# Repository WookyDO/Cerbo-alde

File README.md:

# Cerbo-alde

Steuerung einer **Alde Compact 3030 Plus** oder einer **Truma Combi mit CP Plus** über den
**Cerbo GX** (Venus OS) oder eine eigene Weboberfläche, mit dem **WomoLIN LIN-Controller**
(ESP32 + TJA1021T) als Bridge am LIN-Bus der Heizung.

```
Alde 3030 Plus ── gelber RJ12 ──┐
  (Bridge = LIN-Master)         ├─ WomoLIN LIN-Controller ── WLAN/TCP ── Cerbo GX
Truma CP Plus  ── RJ12 (TIN) ───┘    Firmware: firmware/                 Dienst: cerbo/dbus-lin-heater/
  (Bridge = iNet Box, LIN-Slave)     Weboberfläche: http://lin-bridge.local
```

Der Heizungstyp wird auf der Setup-Seite der Bridge gewählt. Der Cerbo-Dienst übernimmt ihn
automatisch.

> **Status:** Protokolle und Logik sind mit Unit-Tests geprüft. Beide Typen laufen im Testbetrieb
> auf dem Controller und dem Cerbo. Der Test an einer echten Alde und an einem echten CP Plus steht
> noch aus. Erst nur lesen (siehe [Inbetriebnahme](#inbetriebnahme)), dann steuern.

## Auf dem Cerbo

**Alde Compact 3030 Plus**

| D-Bus-Dienst | Inhalt |
|---|---|
| `com.victronenergy.switch.alde_3030` | Sollwert (Temperaturregler), Gas ein/aus, Elektro 1/2/3 kW, Warmwasser Aus/An/Boost; Statuswerte unter `/Alde/*` (Pumpe, Gasventil, 230 V, Fehler) |
| `com.victronenergy.temperature.alde_innen` | Innentemperatur |
| `com.victronenergy.temperature.alde_aussen` | Außentemperatur |

**Truma Combi mit CP Plus**

| D-Bus-Dienst | Inhalt |
|---|---|
| `com.victronenergy.switch.truma_combi` | Raumtemperatur (Temperaturregler mit an/aus), Heizstufe Aus/Eco/Boost, Warmwasser Aus/Eco/Heiß/Boost, Energie Gas/Mix/Elektro, Elektro 900/1800 W; Statuswerte unter `/Truma/*` (Betriebsstatus, Fehlercode) |
| `com.victronenergy.temperature.truma_innen` | Innentemperatur |
| `com.victronenergy.temperature.truma_wasser` | Wassertemperatur |

In der GUI v2 erscheinen die Schalter in der Schalter-Ansicht (Gruppe „Alde Heizung“ bzw.
„Truma Heizung“), die Temperaturen unter Temperatursensoren und im VRM.

## Hardware

**ESP32_LIN-Platine** (ESP32-C3-WROOM-02-N4, 2× TJA1021T/20, KiCad-Projekt in [`hardware/`](hardware), Fertigungsdaten in `hardware/fertigung`):

| | Truma (Bridge = Slave) | Alde (Bridge = Master) |
|---|---|---|
| Kanal | LIN1, Klemme J2 / RJ12 J6 | LIN2, Klemme J5 / RJ12 J7, **Jumper JP1 stecken** |
| GPIO RX / TX / SLP | 5 / 6 / 7 | 4 / 10 / 20 |

- Nur der Transceiver der gewählten Heizung wird geweckt (SLP high), der andere schläft.
- Rote LED (GPIO8, aktiv low): an = Heizung verbunden und Netz da, blinkt = Setup- oder
  Notfall-Access-Point offen, aus = keine Verbindung zur Heizung. Grün = Versorgung.
- Bordspannung über VSENSE (GPIO3, Teiler 100k/15k an VIN_F): in der Weboberfläche,
  `/api/state` (`"vin"`), per Befehl `VIN` und in `NET`. Gemessen wird hinter der
  Verpolschutz-Diode; der Wert enthält dafür pauschal 0,24 V (`VSENSE_DIODE_DROP` in `config.h`,
  gemessen bei 12 V). Nur an USB ist die Anzeige nicht aussagekräftig, weil der Strom dort über
  D3 statt über D1 kommt.
- RJ12-Buchsen in Truma-Belegung: Pin 1 = 12 V (VIN_RAW), Pin 2/5 = GND, Pin 3 = LIN.
  Der gelbe Alde-Stecker hat LIN auf Pin 4 und passt deshalb nicht direkt an J7; die Alde
  über die Klemme J5 anschließen.
- Flashen und Log über USB-C (USB-Serial/JTAG des C3, keine Treiber nötig).

**WomoLIN LIN-Controller:**

- WomoLIN LIN-Controller: ESP32 (16 MB), TJA1021T, LIN an UART1 (**RX GPIO14, TX GPIO15**),
  LEDs GPIO2 (LIN) und GPIO17 (Netz). Pinbelegung aus `inetbox2mqtt` (Profil `WOMOLIN`).
- **Alde:** Anschluss am **gelben** RJ12: **Pin 4 = LIN**, **Pin 2 = GND**. Den roten (internen) Bus
  nicht verwenden.
- **Truma:** Anschluss am RJ12 des CP Plus bzw. TIN-Bus: **Pin 3 = LIN**, **Pin 5 = GND**.
  Voraussetzungen: CP Plus mit Firmware **ab C4.00.00** (ältere nur lesen), **keine echte iNet Box**
  am Bus (war je eine angeschlossen, vorher ohne Bridge einmal neu initialisieren). Getestet ist das
  Protokoll in den Quellen mit der Combi 4.
- 12 V für den Controller aus dem Bordnetz. Die Masse muss mit der Heizung verbunden sein.

## Firmware (`firmware/`)

Benötigt [PlatformIO](https://platformio.org/).

```sh
cd firmware
pio run -e esp32_lin -t upload  # ESP32_LIN: erstes Flashen per USB
pio run -e womolin -t upload    # WomoLIN: erstes Flashen per USB
pio device monitor              # Logausgabe, 115200 Baud
```

Für OTA und den Testbetrieb gibt es zu jeder Platine die Varianten `_ota`, `_sim` und `_sim_ota`
(z.B. `esp32_lin_ota`).

WLAN, IP, Passwörter und Heizungstyp werden nicht einkompiliert, sondern auf der Setup-Seite der
Bridge eingestellt (siehe [Einrichtung](#einrichtung)). Alle weiteren Updates gehen per WLAN:

```sh
export LIN_OTA_PASSWORD='…'    # OTA-Passwort aus der Setup-Seite
pio run -e womolin_ota -t upload
```

Die Originalsoftware lässt sich jederzeit wiederherstellen, über
`bin/flash_womolin_inetbox2mqtt_*.bin.zip` aus [inetbox2mqtt](https://github.com/mc0110/inetbox2mqtt).

Eine Firmware für beide Heizungen: Flash 885 KB von 6,4 MB je App-Partition (13,5 %),
RAM 50 KB von 320 KB (15 %).

### Ablauf auf dem Bus: Alde (Bridge = LIN-Master, 19200 Baud)

- Vor dem ersten Senden hört die Bridge 1,5 s auf den Bus. Die Alde-Bedienteile senden nie von
  sich aus; kommen trotzdem Daten, hängt ein anderer Master am Bus (z.B. ein Truma CP Plus). Dann
  sendet die Bridge nichts, meldet `ERR Fremder LIN-Master am Bus` und prüft alle 10 s erneut.
- Beim Start und nach Verbindungsverlust (alle 5 s) wird der Anmelde-Frame `0x3C` gesendet:
  `10 06 B2 00 DE 41 03 00`.
- Alle 500 ms wird der Info-Frame `0x1B` (PID `0x5B`) abgefragt. Das eigene Echo wird verworfen,
  die Antwort wird anhand der Checksumme erkannt.
- Ein Steuer-Frame `0x1A` geht **nur bei einem Befehl** raus, als **Read-Modify-Write** auf Basis des
  zuletzt gelesenen Zustands. Statusbits und Zone 2 bleiben unverändert. Danach wird bis zu
  5-mal abgefragt, ob das Panel den Befehl übernommen hat. Es gibt maximal 3 Sendeversuche.
- Break: `0x00` bei 9600 Baud, das sind etwa 0,94 ms bzw. 18 Bitzeiten bei 19200 Baud.

### Ablauf auf dem Bus: Truma (Bridge = iNet Box, LIN-Slave, 9600 Baud)

- Das CP Plus ist Master. Die Bridge antwortet in einer eigenen FreeRTOS-Task, damit Webserver und
  WLAN die Antwortzeit nicht verzögern.
- Anmeldung (nach „PR SET“ am CP Plus): Lesen der Kennung `0xB2` (Supplier `0x4617`, Function
  `0x1F00`), Zuweisen der Knotenadresse `0xB0` (NAD `0x03`), danach regelmäßig `0xB9`.
- Das CP Plus schickt seinen Status als Puffer `0x14/0x33` über den Transport-Layer (`0x3C`,
  Dienst `0xBB`, 7 Frames). Temperaturen sind Kelvin × 10.
- Auf PID `0x18` meldet die Bridge `FF`, wenn ein Befehl bereitliegt, sonst `FE`. Das CP Plus holt
  ihn dann mit `0xBA` ab (Puffer `0x0C/0x32` auf `0x3D`). Unveränderte Felder werden aus dem
  letzten Status übernommen.
- Das CP Plus fragt nicht ständig; Pausen von 15–25 s sind normal. Bis ein Befehl im Status
  bestätigt ist, können ~30 s vergehen. Ohne Bestätigung nach 60 s wird er erneut eingereiht,
  insgesamt 3 Versuche.
- Regeln des CP Plus, die die Bridge selbst ergänzt: Raumtemperatur und Heizstufe gehören
  zusammen (Sollwert ab 5 °C schaltet Eco ein, Heizstufe „aus“ setzt den Sollwert auf 0), ebenso
  Energie und Leistung (Gas = 0 W, Mix/Elektro = 900 oder 1800 W).

### Zeilenprotokoll (TCP-Port 7020 und USB-Seriell)

Beim Verbinden meldet die Bridge `HELLO lin-bridge 1.1 heater=alde` bzw. `heater=truma`.
Zeilen mit `#` sind Logausgaben.

| Richtung | Zeile | Bedeutung |
|---|---|---|
| → | `GET` / `PING` | Zustand senden / `PONG` |
| → | `SET …` | siehe unten, beliebige Teilmenge |
| ← | `STATE link=1 …` | bei Änderung, sonst alle 5 s |
| ← | `STATE link=0` | Heizung antwortet nicht |
| ← | `OK` / `ERR <Text>` | Befehl angenommen / abgelehnt oder nicht übernommen |

| Heizung | `SET` | `STATE` |
|---|---|---|
| Alde | `sp` 5–30 °C (0,5er Schritte), `gas` 0/1, `el` 0–3 kW, `ww` 0=aus 1=an 2=Boost | `STATE link=1 z1=21.0 z2=- out=8.0 sp=20.0 gas=1 valve=1 el=2 ww=1 on=1 busy=0 err=0 ac=1 pump=1 raw=DE9E29` |
| Truma | `sp` 0 oder 5–30 °C, `mode` off/eco/boost, `ww` 0/40/60/200 (aus/Eco/heiß/Boost), `mix` gas/mix/el, `el` 0/900/1800 W | `STATE link=1 room=19.5 sp=21.0 mode=eco water=48.0 ww=60 mix=gas el=0 status=5 err=0` |

Typspezifische Befehle: `DIAG` (Alde: Anmelde-Frame erneut senden), `LINLOG 1`/`LINLOG 0`
(Truma: alle Frames am Bus als Logzeilen ausgeben).

Zum Testen: `nc <ip> 7020` oder den seriellen Monitor verwenden. Die Bridge hält nur eine
TCP-Verbindung; eine neue verdrängt die bestehende (z.B. die des Cerbo).

### Weboberfläche (Betrieb ohne Cerbo)

Unter `http://lin-bridge.local` (oder der IP der Bridge) gibt es eine Seite mit dem gleichen
Umfang wie auf dem Cerbo, passend zum Heizungstyp. Dazu kommen die WLAN-Signalstärke und ein Link
zu den Einstellungen. Befehle laufen über denselben Weg wie die vom Cerbo; beide lassen sich
gleichzeitig verwenden.

| Pfad | Methode | Inhalt |
|---|---|---|
| `/` | GET | Weboberfläche |
| `/api/state` | GET | `{"type":"alde"\|"truma","state":{…}\|null,"pending":bool,"error":"…","rssi":-67,"ap":bool}` |
| `/api/set` | POST | Formularfelder wie bei `SET`; Antwort `{"ok":true}` oder `{"ok":false,"error":"…"}` |
| `/setup` | GET | Einstellungen |
| `/api/config` | GET / POST | Einstellungen lesen (ohne Passwörter) / speichern |
| `/api/scan` | GET | WLAN-Suche, so lange abfragen bis `"scanning":false` |

Mit einem Web-Passwort (Setup-Seite) sind alle Seiten geschützt, Benutzer `admin`. Ohne ist die
Bridge für jeden im selben WLAN bedienbar, auch die Einstellungen.

### Einrichtung

Die Einstellungen liegen im Flash der Bridge (NVS) und überstehen Firmware-Updates.

| Einstellung | Bedeutung |
|---|---|
| Heizung | Alde Compact 3030 Plus oder Truma Combi mit CP Plus. Ein Wechsel startet die Bridge neu. |
| Betriebsart | **WLAN-Client**: Die Bridge verbindet sich mit dem Router. **Eigener Access Point**: Die Bridge öffnet dauerhaft ein eigenes WLAN, IP `192.168.4.1`. Der Cerbo verbindet sich dann mit diesem WLAN und bekommt `host = 192.168.4.1` in `config.ini`. |
| WLAN | Netzwerk (mit Suche) und Passwort |
| IP-Adresse | DHCP oder fest (IP, Gateway, Subnetzmaske, DNS). Eine feste Adresse muss außerhalb des DHCP-Bereichs liegen, bei der Fritzbox standardmäßig `.20`–`.200`. |
| Access Point | Name (Standard `LIN-Bridge`) und Passwort (Standard `lin-setup`, solange kein eigenes gesetzt ist) |
| OTA-Passwort | Pflicht. Updates per WLAN sind erst nach der Einrichtung möglich, nie ohne Passwort. |
| Web-Passwort | optional, Benutzer `admin` |

Speichern ohne Änderung tut nichts. Neue OTA- oder Web-Passwörter gelten sofort. Bei allem anderen
startet die Bridge neu; die Seite wartet, bis sie wieder antwortet.

**Erster Start:** Ohne gespeicherte Einstellungen öffnet die Bridge den Access Point `LIN-Bridge`
(Passwort `lin-setup`). Nach dem Verbinden öffnen die meisten Handys die Setup-Seite von selbst,
sonst `http://192.168.4.1` aufrufen.

**Notfall-Zugang:** Ist das eingestellte WLAN 60 s nicht erreichbar (falsches Passwort, Router aus),
öffnet die Bridge zusätzlich ihren Access Point und versucht alle 30 s erneut, ins WLAN zu kommen.
Sobald das klappt und niemand mehr am Access Point hängt, schließt sie ihn wieder. Die Netz-LED
blinkt, solange der Access Point offen ist.

**Rettung über USB:** Ist die Bridge nicht mehr erreichbar, nimmt sie über die USB-Schnittstelle
(115200 Baud) diese Befehle an. Über TCP sind sie gesperrt.

| Befehl | Wirkung |
|---|---|
| `NET` | Betriebsart, WLAN, IP-Adressen und Heizungstyp anzeigen |
| `NET STA` | zurück auf WLAN-Client (gespeichertes WLAN), Neustart |
| `NET AP` | auf dauerhaften Access Point (braucht ein gespeichertes AP-Passwort), Neustart |

Nach einer Änderung der Adresse `host` in `config.ini` auf dem Cerbo anpassen.

## Cerbo-Dienst (`cerbo/dbus-lin-heater/`)

Voraussetzung ist SSH-Zugang als root: Einstellungen → Allgemein → Zugriffsebene „Superuser“,
Root-Passwort setzen, SSH im LAN aktivieren.

```sh
scp -r cerbo/dbus-lin-heater root@<cerbo-ip>:/data/
ssh root@<cerbo-ip> /data/dbus-lin-heater/install.sh
ssh root@<cerbo-ip> vi /data/dbus-lin-heater/config.ini   # host = IP der Bridge
ssh root@<cerbo-ip> svc -t /service/dbus-lin-heater       # neu starten
```

- Heizungstyp: Mit `heater = auto` (Standard) übernimmt der Dienst den Typ aus dem `HELLO` der
  Bridge. Meldet sie einen anderen als den laufenden, merkt er ihn sich und startet mit den
  passenden D-Bus-Diensten neu. Mit `heater = alde` oder `truma` bleibt er fest; ein abweichender
  Typ wird dann nur gemeldet und nicht ausgewertet.
- Truma: Nach einer Eingabe in der GUI hält der Dienst den neuen Wert 40 s, bis das CP Plus ihn
  bestätigt hat (Alde: 3 s).
- Logs: `tail -F /var/log/dbus-lin-heater/current | tai64nlocal`
- Deinstallieren: `/data/dbus-lin-heater/uninstall.sh`
- Der Dienst übersteht Firmware-Updates, weil er unter `/data` liegt und über `/data/rc.local` gestartet wird.

## Inbetriebnahme

**Alde**

1. Controller flashen, über den Access Point `LIN-Bridge` einrichten, Heizung „Alde“ wählen.
2. Mit der Alde verbinden. Nach `Panel antwortet` sollten `STATE link=1 …`-Zeilen erscheinen.
   Die Werte mit dem Display der Alde vergleichen.
3. Einen einzelnen Befehl testen, z.B. über die Weboberfläche den Sollwert ändern, und am Panel prüfen.
4. Danach den Cerbo-Dienst installieren.

Erscheint dauerhaft `STATE link=0`, prüfe Verdrahtung, Masse und 12 V. Hilft das nicht, mit
einem Logikanalysator am LIN-Pin Break und Antwort prüfen.

**Truma**

1. Controller flashen, einrichten, Heizung „Truma“ wählen.
2. An das CP Plus anschließen und mit `LINLOG 1` (USB oder `nc <ip> 7020`) mithören. Es sollten
   Header `18`, `3C` und `3D` erscheinen. Kommt nach 60 s nichts, meldet die Weboberfläche
   „Kein CP Plus gefunden“.
3. Am CP Plus im Einstellungsmenü **„PR SET“** ausführen. Das Display zeigt „INIT…“, danach steht im
   Menü ein dritter Eintrag `inetbox`. Die Bridge meldet `CP Plus verbunden`.
4. Werte mit dem CP Plus vergleichen, dann einzelne Befehle testen. Bis zur Bestätigung können
   ~30 s vergehen.
5. Danach den Cerbo-Dienst installieren.

### Testbetrieb ohne Heizung

```sh
cd firmware
pio run -e womolin_sim -t upload        # per USB
pio run -e womolin_sim_ota -t upload    # per WLAN
```

- **Alde:** Der Controller beantwortet seine LIN-Abfragen selbst wie ein Alde-Panel. Die Antworten
  laufen über den echten Transceiver und kommen als Echo zurück; Steuer-Frames liest das simulierte
  Panel ebenfalls aus dem Echo. Damit lassen sich LIN-Hardware, WLAN/TCP und der Cerbo-Dienst
  testen. Der Controller braucht dafür 12 V, sonst bleibt es bei `link=0`. Das Panel startet mit
  18 °C innen, 8 °C außen und Sollwert 20 °C und heizt bei Gas oder Elektro mit 0,05 °C/s.
- **Truma:** Ein simuliertes CP Plus spielt den kompletten Transport-Layer in Software gegen die
  iNet Box durch, ohne Bus. Damit lassen sich Weboberfläche, TCP und Cerbo-Dienst testen, nicht aber
  der LIN-Slave-Treiber. Start: 15 °C innen, Wasser 20 °C, Heizung aus.

Die Testvariante **nicht an der echten Heizung** verwenden. Vor dem Anschluss wieder
`pio run -e womolin -t upload` (oder per WLAN `womolin_ota`) aufspielen.

## Tests

```sh
cd cerbo/dbus-lin-heater && python3 -m unittest discover -s tests   # Cerbo-Dienst
cd firmware && pio test -e native                                    # Protokolle (C++)
```

## Quellen

- [daviddootson/alde_3030_plus](https://github.com/daviddootson/alde_3030_plus): Protokoll des
  CI-Busses der 3030 Plus (Mitschnitte, Anmelde-Frame, Bitbelegung)
- [danielfett/inetbox.py](https://github.com/danielfett/inetbox.py): Protokoll der Truma iNet Box
  (Transport-Layer, Puffer, Prüfsumme, Referenzwerte für die Tests). Der Code hier ist eine eigene
  Umsetzung nach dieser Beschreibung; inetbox.py steht unter GPL-3.0.
- [mc0110/inetbox2mqtt](https://github.com/mc0110/inetbox2mqtt): Pinbelegung des WomoLIN-Controllers,
  Voraussetzungen und Einrichtung am CP Plus
- [WomoLIN](https://github.com/muccc/WomoLIN): Grundlagen zum LIN-Bus im Wohnmobil
- [victronenergy/gui-v2](https://github.com/victronenergy/gui-v2): Schnittstelle `SwitchableOutput`

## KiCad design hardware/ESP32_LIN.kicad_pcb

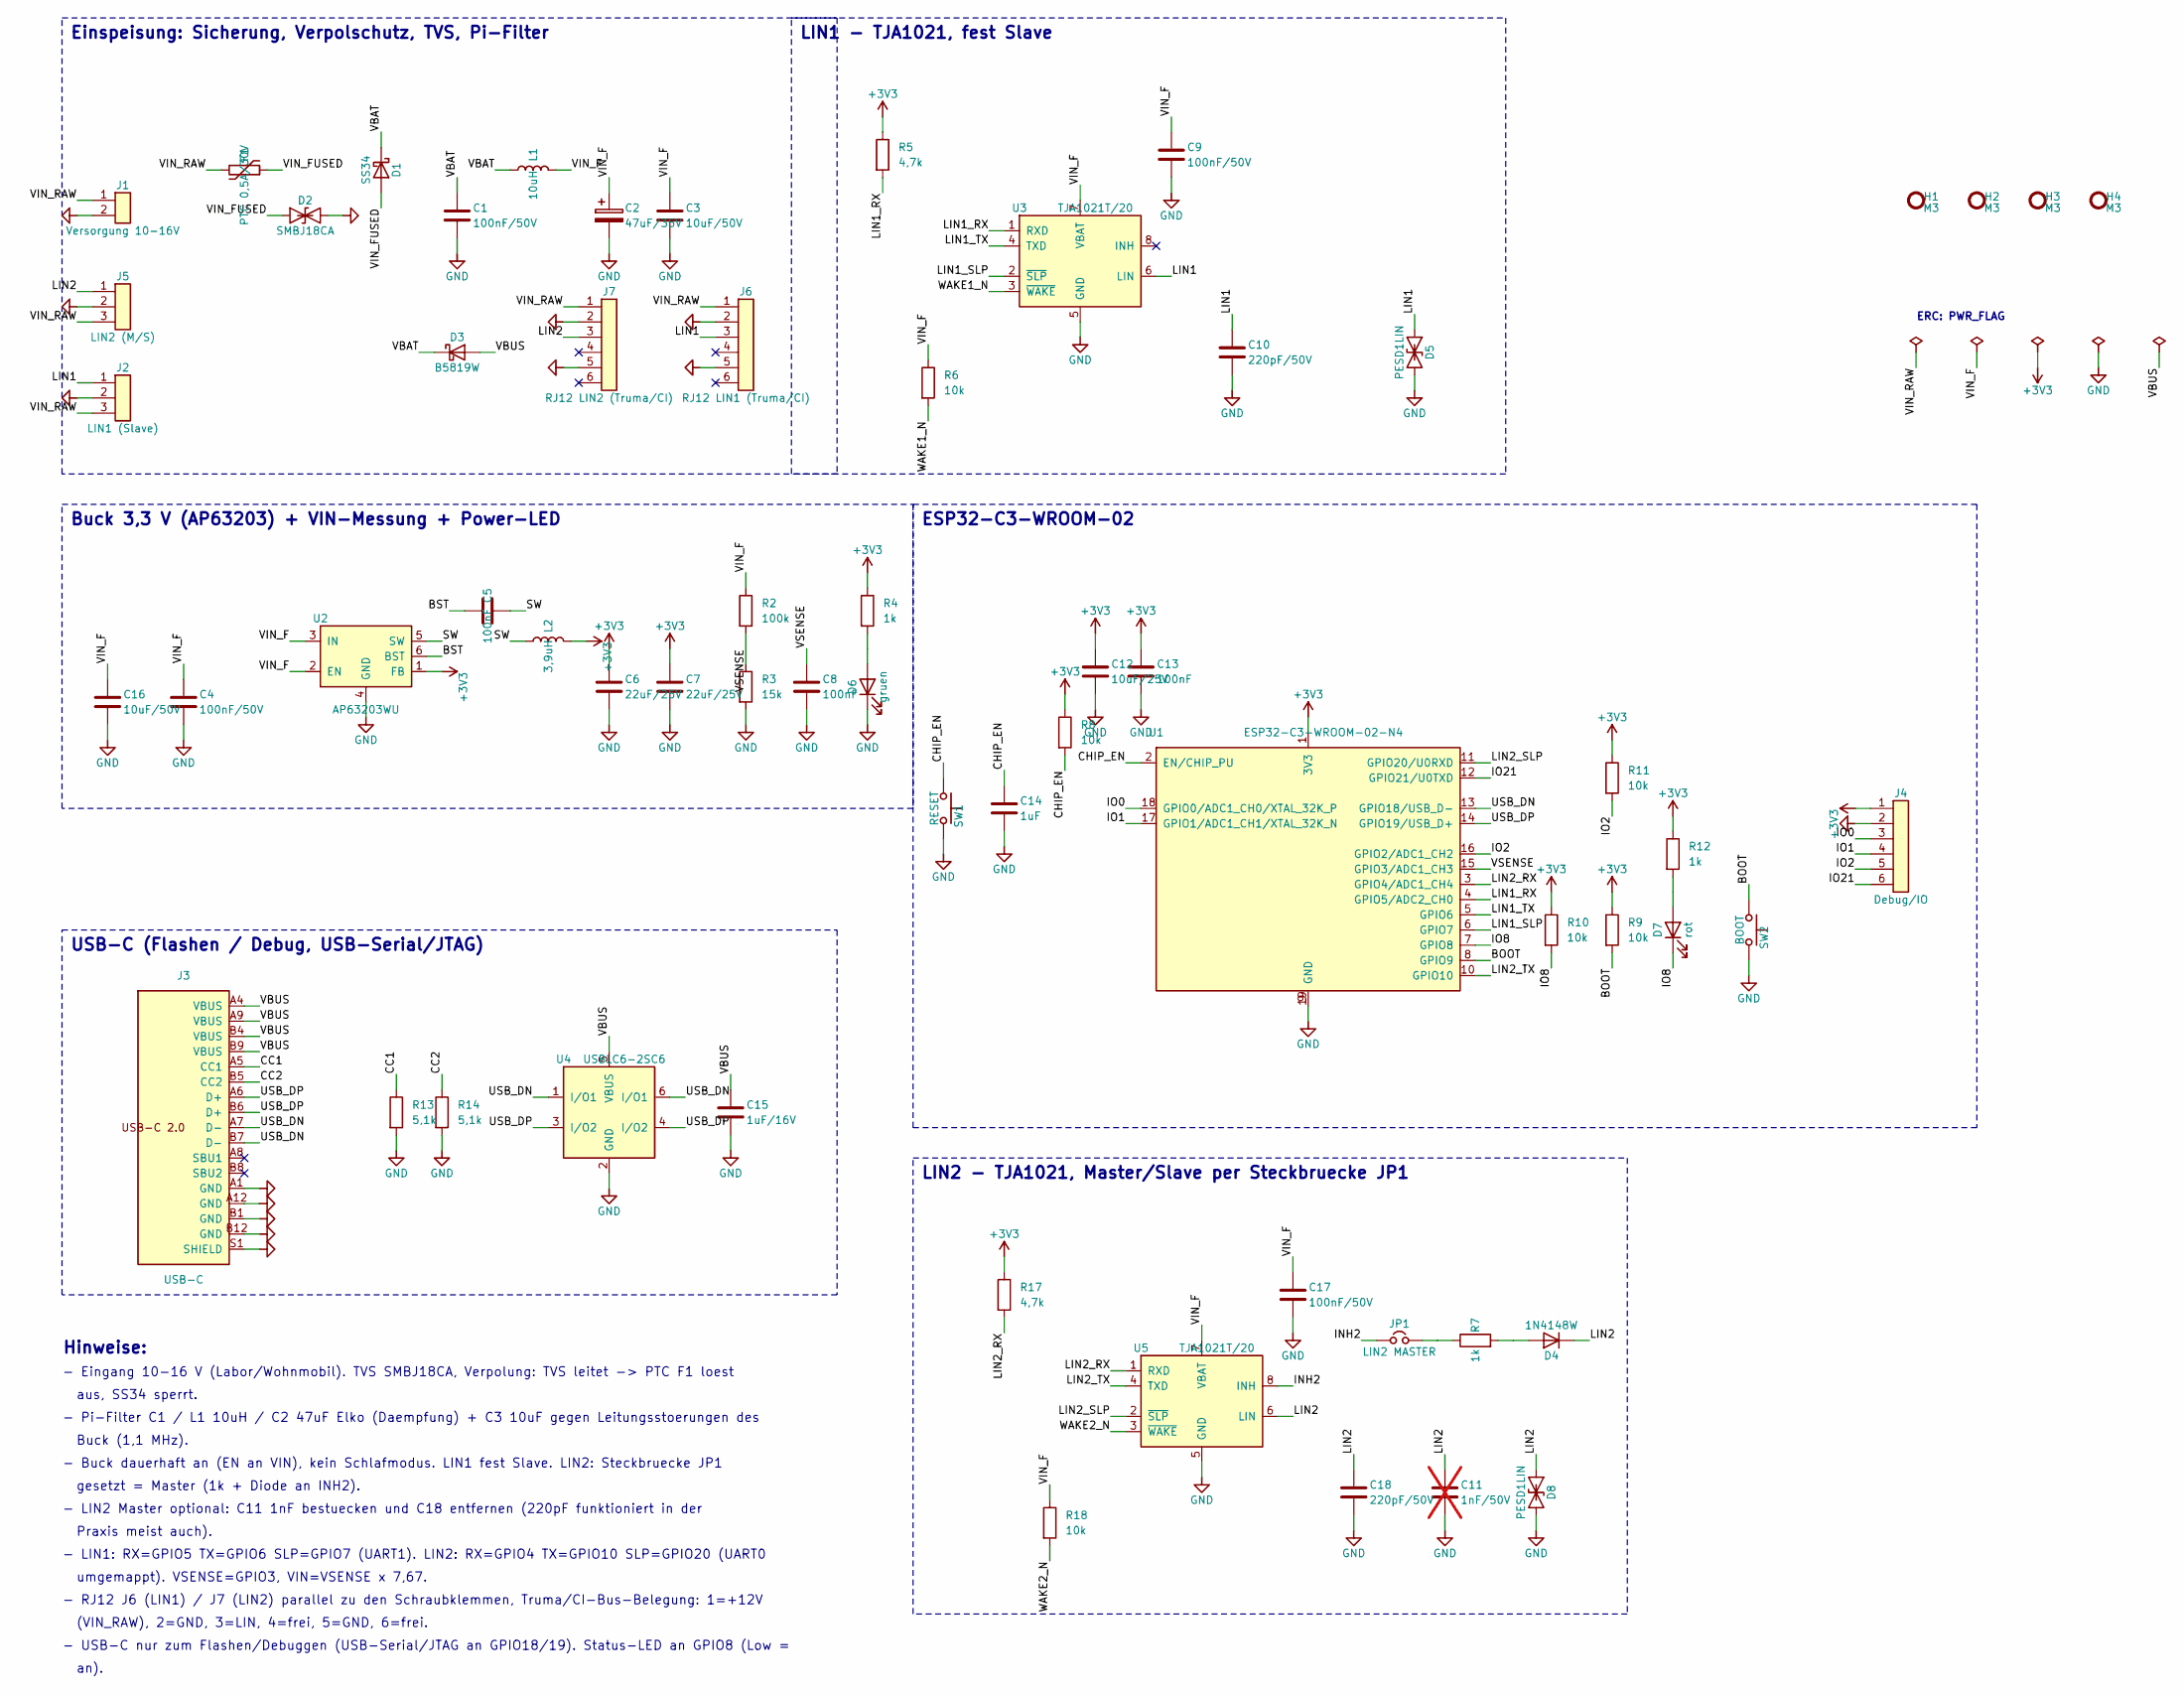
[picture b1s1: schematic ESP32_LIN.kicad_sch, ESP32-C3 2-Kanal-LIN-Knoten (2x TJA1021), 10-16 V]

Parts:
C1, C4, C9, C17: 100nF/50V; C_0603_1608Metric; MPN CC0603KRX7R9BB104; LCSC C14663
C2: 47uF/35V; CP_Elec_6.3x7.7; MPN VEJ470M1VTR-0607; LCSC C122665
C3, C16: 10uF/50V; C_1210_3225Metric; MPN CL32B106KBJNNNE; LCSC C138687
C5, C8, C13: 100nF; C_0603_1608Metric; MPN CC0603KRX7R9BB104; LCSC C14663
C6, C7: 22uF/25V; C_1206_3216Metric; MPN CL31A226KAHNNNE; LCSC C12891
C10, C18: 220pF/50V; C_0603_1608Metric; MPN CL10B221KB8NNNC; LCSC C1603
C11: 1nF/50V; C_0603_1608Metric; MPN CL10B102KB8NNNC; LCSC C1588; not fitted
C12: 10uF/25V; C_0805_2012Metric; MPN CL21A106KAYNNNE; LCSC C15850
C14: 1uF; C_0603_1608Metric; MPN CL10A105KB8NNNC; LCSC C15849
C15: 1uF/16V; C_0603_1608Metric; MPN CL10A105KB8NNNC; LCSC C15849
D1: SS34; D_SMA; MPN SS34; LCSC C115205
D2: SMBJ18CA; D_SMB; MPN SMBJ18CA; LCSC C113991
D3: B5819W; D_SOD-123; MPN B5819W; LCSC C109213
D4: 1N4148W; D_SOD-123; MPN 1N4148W; LCSC C109203
D5, D8: PESD1LIN; D_SOD-323; MPN PESD1LIN; LCSC C393615
D6: gruen; LED_0603_1608Metric; MPN LTST-C190KGKT; LCSC C125094
D7: rot; LED_0603_1608Metric; MPN KT-0603R; LCSC C2286
F1: PTC 0,5A/30V; Fuse_1812_4532Metric; MPN 1812L050/60GR; LCSC C19078719
H1, H2, H3, H4: M3; MountingHole_3.2mm_M3
J1: Versorgung 10-16V; TerminalBlock_Phoenix_MKDS-1,5-2-5.08_1x02_P5.08mm_Horizont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; MPN KF128-5.08-2P-AA; LCSC C474952
J2: LIN1 (Slave); TerminalBlock_Phoenix_MKDS-1,5-3-5.08_1x03_P5.08mm_Horizont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; MPN KF128-5.08-3P-AA; LCSC C474953
J3: USB-C; USB_C_Receptacle_HRO_TYPE-C-31-M-12; MPN TYPE-C-31-M-12; LCSC C165948
J4: Debug/IO; PinHeader_1x06_P2.54mm_Vertical; MPN B-2100S06P-A110; LCSC C124380
J5: LIN2 (M/S); TerminalBlock_Phoenix_MKDS-1,5-3-5.08_1x03_P5.08mm_Horizont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; MPN KF128-5.08-3P-AA; LCSC C474953
J6: RJ12 LIN1 (Truma/CI); TYCO_5555165-1; MPN 5555165-1; LCSC C305981
J7: RJ12 LIN2 (Truma/CI); TYCO_5555165-1; MPN 5555165-1; LCSC C305981
JP1: LIN2 MASTER; PinHeader_1x02_P2.54mm_Vertical; MPN B-2100S02P-A110; LCSC C124375
L1: 10uH; L_Bourns_SRN6045TA; MPN SMNR6045-100MT; LCSC C135304
L2: 3,9uH; L_Bourns-SRN4018; MPN SWPA4030S3R9MT; LCSC C96899
R2: 100k; R_0603_1608Metric; MPN 0603WAF1003T5E; LCSC C25803
R3: 15k; R_0603_1608Metric; MPN 0603WAF1502T5E; LCSC C22809
R4, R12: 1k; R_0603_1608Metric; MPN 0603WAF1001T5E; LCSC C21190
R5, R17: 4,7k; R_0603_1608Metric; MPN 0603WAF4701T5E; LCSC C23162
R6, R8, R9, R10, R11, R18: 10k; R_0603_1608Metric; MPN 0603WAF1002T5E; LCSC C25804
R7: 1k; R_1206_3216Metric; MPN 1206W4F1001T5E; LCSC C4410
R13, R14: 5,1k; R_0603_1608Metric; MPN 0603WAF5101T5E; LCSC C23186
SW1: RESET; SW_SPST_B3U-1000P; MPN B3U-1000P; LCSC C231329
SW2: BOOT; SW_SPST_B3U-1000P; MPN B3U-1000P; LCSC C231329
U1: ESP32-C3-WROOM-02-N4; ESP32-C3-WROOM-02; MPN ESP32-C3-WROOM-02-N4
U2: AP63203WU; TSOT-23-6; MPN AP63203WU-7; LCSC C780769
U3, U5: TJA1021T/20; SOIC-8_3.9x4.9mm_P1.27mm; MPN TJA1021T/20/CM,118; LCSC C128810
U4: USBLC6-2SC6; SOT-23-6; MPN USBLC6-2SC6; LCSC C21713975

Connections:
+3V3: C6.1, C7.1, C12.1, C13.1, J4.1, L2.2, R4.1, R5.1, R8.1, R9.1, R10.1, R11.1, R12.1, R17.1, U1.1 (3V3), U2.1 (FB)
BOOT: R9.2, SW2.1, U1.8 (GPIO9)
BST: C5.1, U2.6 (BST)
CC1: J3.A5 (CC1), R13.1
CC2: J3.B5 (CC2), R14.1
CHIP_EN: C14.1, R8.2, SW1.1, U1.2 (EN/CHIP_PU)
GND: C1.2, C2.2, C3.2, C4.2, C6.2, C7.2, C8.2, C9.2, C10.2, C11.2, C12.2, C13.2, C14.2, C15.2, C16.2, C17.2, C18.2, D2.2 (A2), D5.2 (A2), D6.1 (K), D8.2 (A2), J1.2, J2.2, J3.A1 (GND), J3.A12 (GND), J3.B1 (GND), J3.B12 (GND), J3.S1 (SHIELD), J4.2, J5.2, J6.2, J6.5, J7.2, J7.5, R3.2, R13.2, R14.2, SW1.2, SW2.2, U1.9 (GND), U1.19 (GND), U2.4 (GND), U3.5 (GND), U4.2 (GND), U5.5 (GND)
INH2: JP1.1 (A), U5.8 (INH)
IO0: J4.3, U1.18 (GPIO0/ADC1_CH0/XTAL_32K_P)
IO1: J4.4, U1.17 (GPIO1/ADC1_CH1/XTAL_32K_N)
IO2: J4.5, R11.2, U1.16 (GPIO2/ADC1_CH2)
IO8: D7.1 (K), R10.2, U1.7 (GPIO8)
IO21: J4.6, U1.12 (GPIO21/U0TXD)
LIN1: C10.1, D5.1 (A1), J2.1, J6.3, U3.6 (LIN)
LIN1_RX: R5.2, U1.4 (GPIO5/ADC2_CH0), U3.1 (RXD)
LIN1_SLP: U1.6 (GPIO7), U3.2 (~SLP)
LIN1_TX: U1.5 (GPIO6), U3.4 (TXD)
LIN2: C11.1, C18.1, D4.1 (K), D8.1 (A1), J5.1, J7.3, U5.6 (LIN)
LIN2_PU: JP1.2 (B), R7.1
LIN2_PU2: D4.2 (A), R7.2
LIN2_RX: R17.2, U1.3 (GPIO4/ADC1_CH4), U5.1 (RXD)
LIN2_SLP: U1.11 (GPIO20/U0RXD), U5.2 (~SLP)
LIN2_TX: U1.10 (GPIO10), U5.4 (TXD)
PWR_LED: D6.2 (A), R4.2
STAT_LED: D7.2 (A), R12.2
SW: C5.2, L2.1, U2.5 (SW)
USB_DN: J3.A7 (D-), J3.B7 (D-), U1.13 (GPIO18/USB_D-), U4.1 (I/O1), U4.6 (I/O1)
USB_DP: J3.A6 (D+), J3.B6 (D+), U1.14 (GPIO19/USB_D+), U4.3 (I/O2), U4.4 (I/O2)
VBAT: C1.1, D1.1 (K), D3.1 (K), L1.1
VBUS: C15.1, D3.2 (A), J3.A4 (VBUS), J3.A9 (VBUS), J3.B4 (VBUS), J3.B9 (VBUS), U4.5 (VBUS)
VIN_F: C2.1, C3.1, C4.1, C9.1, C16.1, C17.1, L1.2, R2.1, R6.1, R18.1, U2.2 (EN), U2.3 (IN), U3.7 (VBAT), U5.7 (VBAT)
VIN_FUSED: D1.2 (A), D2.1 (A1), F1.2
VIN_RAW: F1.1, J1.1, J2.3, J5.3, J6.1, J7.1
VSENSE: C8.1, R2.2, R3.1, U1.15 (GPIO3/ADC1_CH3)
WAKE1_N: R6.2, U3.3 (~WAKE)
WAKE2_N: R18.2, U5.3 (~WAKE)

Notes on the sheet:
ERC: PWR_FLAG
Einspeisung: Sicherung, Verpolschutz, TVS, Pi-Filter
Buck 3,3 V (AP63203) + VIN-Messung + Power-LED
LIN1 - TJA1021, fest Slave
LIN2 - TJA1021, Master/Slave per Steckbruecke JP1
ESP32-C3-WROOM-02
USB-C (Flashen / Debug, USB-Serial/JTAG)
Hinweise:
- Eingang 10-16 V (Labor/Wohnmobil). TVS SMBJ18CA, Verpolung: TVS leitet -> PTC F1 loest
aus, SS34 sperrt.
- Pi-Filter C1 / L1 10uH / C2 47uF Elko (Daempfung) + C3 10uF gegen Leitungsstoerungen des
Buck (1,1 MHz).
- Buck dauerhaft an (EN an VIN), kein Schlafmodus. LIN1 fest Slave. LIN2: Steckbruecke JP1
gesetzt = Master (1k + Diode an INH2).
- LIN2 Master optional: C11 1nF bestuecken und C18 entfernen (220pF funktioniert in der
Praxis meist auch).
- LIN1: RX=GPIO5 TX=GPIO6 SLP=GPIO7 (UART1). LIN2: RX=GPIO4 TX=GPIO10 SLP=GPIO20 (UART0
umgemappt). VSENSE=GPIO3, VIN=VSENSE x 7,67.
- RJ12 J6 (LIN1) / J7 (LIN2) parallel zu den Schraubklemmen, Truma/CI-Bus-Belegung: 1=+12V
(VIN_RAW), 2=GND, 3=LIN, 4=frei, 5=GND, 6=frei.
- USB-C nur zum Flashen/Debuggen (USB-Serial/JTAG an GPIO18/19). Status-LED an GPIO8 (Low =
an).

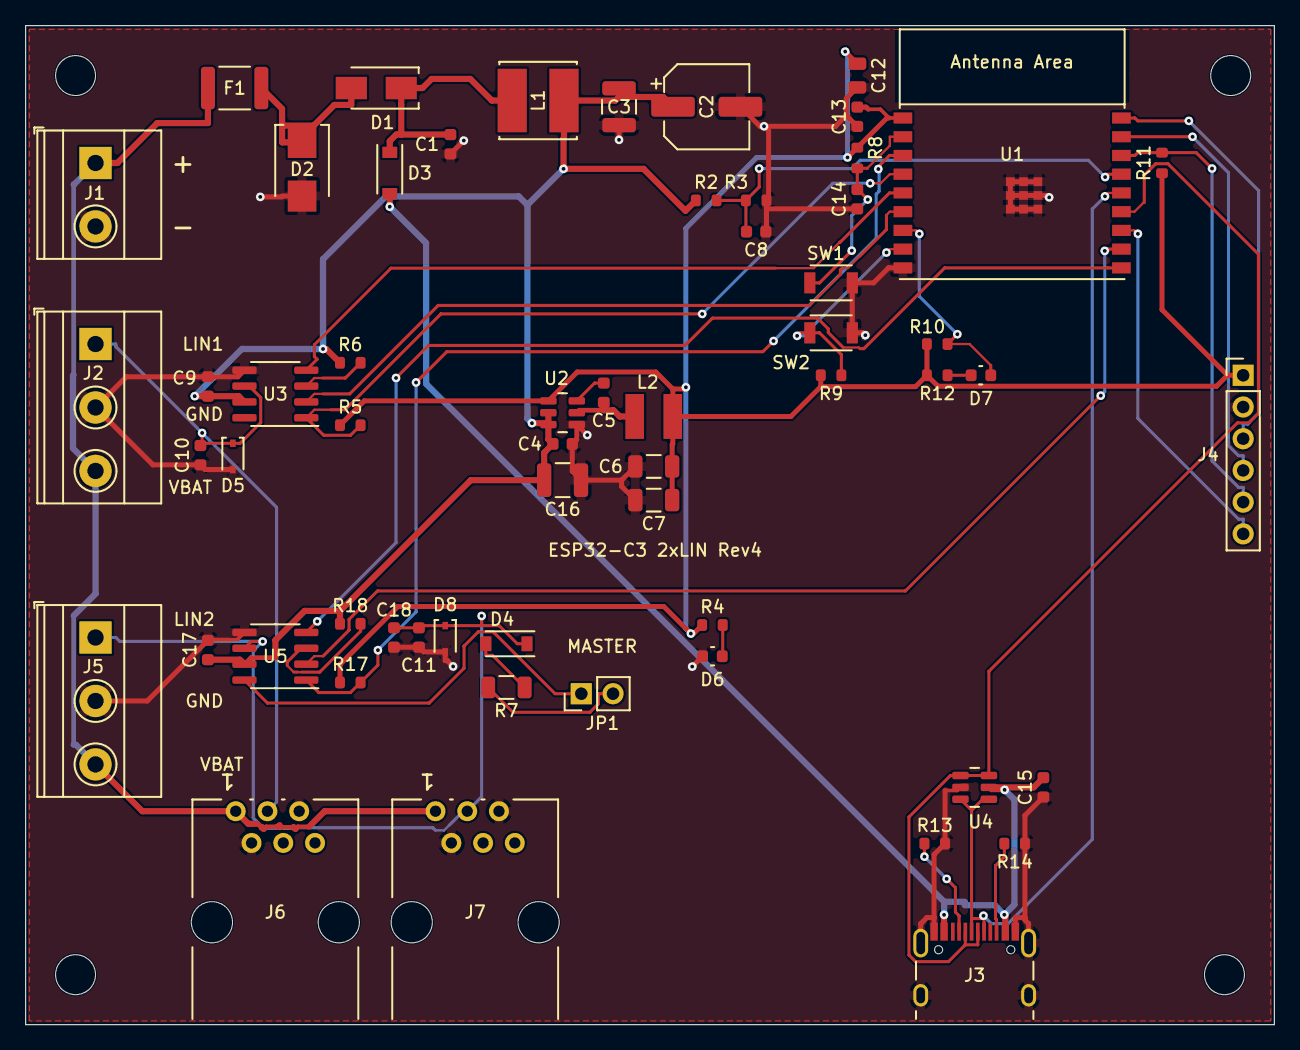
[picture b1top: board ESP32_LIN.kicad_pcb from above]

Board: 2 copper layers, 100.0 x 80.0 mm, 63 parts (0 on the bottom side), 36 nets.

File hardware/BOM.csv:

Referenzen;Anzahl;Wert;Footprint;LCSC;Hersteller-Teil;Hersteller;Bestueckung
SW1, SW2;2;B3U-1000P;SW_SPST_B3U-1000P;C231329;B3U-1000P;Omron;JLCPCB
D3;1;B5819W;D_SOD-123;C109213;B5819W;MDD;JLCPCB
R5, R17;2;4.7kΩ;R_0603_1608Metric;C23162;0603WAF4701T5E;UNI-ROYAL;JLCPCB
C6, C7;2;22uF 25V X5R;C_1206_3216Metric;C12891;CL31A226KAHNNNE;Samsung;JLCPCB
U1;1;ESP32-C3 Modul;ESP32-C3-WROOM-02;;ESP32-C3-WROOM-02-N4;Espressif;selbst beschaffen/loeten
C1, C4, C5, C8, C9, C13, C17;7;100nF 50V X7R;C_0603_1608Metric;C14663;CC0603KRX7R9BB104;YAGEO;JLCPCB
R6, R8, R9, R10, R11, R18;6;10kΩ;R_0603_1608Metric;C25804;0603WAF1002T5E;UNI-ROYAL;JLCPCB
J4;1;Stiftleiste 1x6 2,54 mm;PinHeader_1x06_P2.54mm_Vertical;;PREC006SAAN-RC;Sullins;selbst beschaffen/loeten
JP1;1;Stiftleiste 1x2 2,54 mm;PinHeader_1x02_P2.54mm_Vertical;;PREC002SAAN-RC;Sullins;selbst beschaffen/loeten
C3, C16;2;10uF 50V X7R;C_1210_3225Metric;C138687;CL32B106KBJNNNE;Samsung;JLCPCB
R13, R14;2;5.1kΩ;R_0603_1608Metric;C23186;0603WAF5101T5E;UNI-ROYAL;JLCPCB
J2, J5;2;Schraubklemme 3-pol. 5,08 mm;TerminalBlock_Phoenix_MKDS-1,5-3-5.08_1x03_P5.08mm_Horizontal;;1715734;Phoenix Contact;selbst beschaffen/loeten
J6, J7;2;RJ12 6P6C liegend;TYCO_5555165-1;;5555165-1;TE Connectivity;selbst beschaffen/loeten
D5, D8;2;PESD1LIN;D_SOD-323;C393615;PESD1LIN;DOWO;JLCPCB
F1;1;PTC 0.5A 60V;Fuse_1812_4532Metric;C19078719;1812L050/60GR;Littelfuse;JLCPCB
L2;1;3.9uH;L_Bourns-SRN4018;C96899;SWPA4030S3R9MT;Sunlord;JLCPCB
J3;1;TYPE-C-31-M-12;USB_C_Receptacle_HRO_TYPE-C-31-M-12;C165948;TYPE-C-31-M-12;Korean Hroparts;JLCPCB
C2;1;47uF 35V;CP_Elec_6.3x7.7;C122665;VEJ470M1VTR-0607;Lelon;JLCPCB
U4;1;USBLC6-2SC6;SOT-23-6;C21713975;USBLC6-2SC6;ST;JLCPCB
D4;1;1N4148W;D_SOD-123;C109203;1N4148W;MDD;JLCPCB
R3;1;15kΩ;R_0603_1608Metric;C22809;0603WAF1502T5E;UNI-ROYAL;JLCPCB
U3, U5;2;TJA1021T/20;SOIC-8_3.9x4.9mm_P1.27mm;C128810;TJA1021T/20/CM,118;NXP;JLCPCB
D6;1;LED green;LED_0603_1608Metric;C125094;LTST-C190KGKT;Lite-On;JLCPCB
D1;1;SS34;D_SMA;C115205;SS34;MDD;JLCPCB
C11;1;1nF/50V;C_0603_1608Metric;C1588;CL10B102KB8NNNC;Samsung;NICHT bestuecken
R7;1;1kΩ 0.25W;R_1206_3216Metric;C4410;1206W4F1001T5E;UNI-ROYAL;JLCPCB
L1;1;10uH;L_Bourns_SRN6045TA;C135304;SMNR6045-100MT;Sunlord;JLCPCB
U2;1;AP63203WU-7;TSOT-23-6;C780769;AP63203WU-7;Diodes;JLCPCB
C10, C18;2;220pF 50V X7R;C_0603_1608Metric;C1603;CL10B221KB8NNNC;Samsung;JLCPCB
D2;1;SMBJ18CA;D_SMB;C113991;SMBJ18CA;Littelfuse/LGE;JLCPCB
C12;1;10uF 25V X5R;C_0805_2012Metric;C15850;CL21A106KAYNNNE;Samsung;JLCPCB
C14, C15;2;1uF 50V X5R;C_0603_1608Metric;C15849;CL10A105KB8NNNC;Samsung;JLCPCB
R2;1;100kΩ;R_0603_1608Metric;C25803;0603WAF1003T5E;UNI-ROYAL;JLCPCB
D7;1;LED red;LED_0603_1608Metric;C2286;KT-0603R;Hubei KENTO;JLCPCB
R4, R12;2;1kΩ;R_0603_1608Metric;C21190;0603WAF1001T5E;UNI-ROYAL;JLCPCB
J1;1;Schraubklemme 2-pol. 5,08 mm;TerminalBlock_Phoenix_MKDS-1,5-2-5.08_1x02_P5.08mm_Horizontal;;1715721;Phoenix Contact;selbst beschaffen/loeten

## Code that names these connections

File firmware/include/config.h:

// Hardware- und Netzwerkeinstellungen der LIN-Heizungs-Bridge.
// WLAN, IP und Passwörter werden auf der Setup-Seite eingestellt (settings.h).
#pragma once

#include <cstdint>

// Anschluss eines LIN-Transceivers; slp < 0: SLP fest verdrahtet.
struct LinPins {
  int rx, tx, slp;
};

#if defined(BOARD_ESP32_LIN)
// ESP32_LIN-Platine (ESP32-C3-WROOM-02, 2× TJA1021T/20)
//   LIN1 (J2/J6): fest Slave           -> Truma (Bridge = iNet Box)
//   LIN2 (J5/J7): Master mit JP1       -> Alde  (Bridge = LIN-Master)
constexpr LinPins LIN_TRUMA = {5, 6, 7};   // LIN1_RX, LIN1_TX, LIN1_SLP
constexpr LinPins LIN_ALDE = {4, 10, 20};  // LIN2_RX, LIN2_TX, LIN2_SLP
// Nur eine schaltbare LED (rot, D7 an GPIO8, aktiv low); die grüne ist die
// Power-LED. An: Heizung verbunden und Netz da, blinkt: Setup-/Notfall-AP offen.
constexpr int PIN_LED_STATUS = 8;
// Spannungsteiler 100k/15k an VIN_F, also hinter PTC und Verpolschutz-Diode.
constexpr int PIN_VSENSE = 3;
constexpr int VSENSE_SAMPLES = 32;
constexpr float VSENSE_RATIO = (100.0f + 15.0f) / 15.0f;
constexpr float VSENSE_DIODE_DROP = 0.24f;  // D1 und PTC, gemessen bei 12 V
#else
// WomoLIN LIN-Controller (Pinbelegung wie inetbox2mqtt, Profil "WOMOLIN"),
// ein Transceiver für beide Heizungen.
constexpr LinPins LIN_TRUMA = {14, 15, -1};
constexpr LinPins LIN_ALDE = {14, 15, -1};
constexpr int PIN_LED_LIN = 2;   // aktiv low
constexpr int PIN_LED_NET = 17;  // aktiv low
#endif

constexpr const char *HOSTNAME = "lin-bridge";
constexpr uint16_t TCP_PORT = 7020;
constexpr uint16_t HTTP_PORT = 80;

// Access Point für Ersteinrichtung und als Notfall-Zugang
constexpr const char *SETUP_AP_SSID = "LIN-Bridge";
constexpr const char *SETUP_AP_PASSWORD = "lin-setup";  // solange kein eigenes gesetzt ist
constexpr uint32_t FALLBACK_AP_AFTER_MS = 60000;  // WLAN so lange weg -> AP zusätzlich an
constexpr uint32_t STA_RETRY_MS = 30000;          // neuer Verbindungsversuch zum WLAN

constexpr uint32_t POLL_INTERVAL_MS = 500;      // normale Statusabfrage
constexpr uint32_t CONFIRM_INTERVAL_MS = 300;   // Abfrage nach einem Befehl
constexpr uint32_t STATE_HEARTBEAT_MS = 5000;   // STATE auch ohne Änderung
constexpr uint8_t LINK_LOST_AFTER = 6;          // Fehlversuche bis link=0
constexpr uint8_t COMMAND_RETRIES = 3;          // Sendeversuche pro Befehl
constexpr uint8_t COMMAND_CONFIRM_POLLS = 5;    // Abfragen je Sendeversuch
